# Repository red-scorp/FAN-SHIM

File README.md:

# FAN-SHIM project

FAN-SHIM (mini-HAT), support board for axial fans to cool Raspberry Pi.

Some Pis not require cooling because their CPUs are running in low performance mode.
Some Pis are good with simple passive heat sinks alone.
It's generally recommended to use active coolers, specially if you run Pi's CPU over-clocked.

This boards are designed to be used with standard axial funs with Pi's "Dupont" and standard PC's "Molex" connectors.

## FAN-zero30-SHIM

Raspberry Pi zero 40-pin **FAN-zero30-SHIM** mini-HAT.

Preview:

[Schematics in PDF format](doc/FAN-zero30-SHIM.pdf)

Features:

- locked Pi headers
- 30mm axial fan
- 5V and 3.3V fan power selection
- fan tacho and PWM signal selection
- Pi zero board style
- can be used as SHIM (no headers) or HAT (with headers)

Pins Configuration:

|Fan Pin |Option 1 |Option 2 |
|--------|---------|---------|
|Vfan    |5V\*     |3.3V     |
|tacho   |GPIO16   |GPIO4    |
|PWM     |GPIO12   |GPIO13   |

\*) the pin is connected by default.

CAM files are available.

## FAN-zero25-SHIM

Raspberry Pi zero 40-pin **FAN-zero25-SHIM** mini-HAT.

Preview:

[Schematics in PDF format](doc/FAN-zero25-SHIM.pdf)

Features:

- locked Pi headers
- 25mm axial fan
- 5V and 3.3V fan power selection
- fan tacho and PWM signal selection
- Pi zero board style
- can be used as SHIM (no headers) or HAT (with headers)

Pins Configuration:

|Fan Pin |Option 1 |Option 2 |
|--------|---------|---------|
|Vfan    |5V\*     |3.3V     |
|tacho   |GPIO16   |GPIO4    |
|PWM     |GPIO12   |GPIO13   |

\*) the pin is connected by default.

CAM files are available.

## FAN-zero20-SHIM

Raspberry Pi zero 40-pin **FAN-zero20-SHIM** mini-HAT.

Preview:

[Schematics in PDF format](doc/FAN-zero20-SHIM.pdf)

Features:

- locked Pi headers
- 20mm axial fan
- 5V and 3.3V fan power selection
- fan tacho and PWM signal selection
- Pi zero board style
- can be used as SHIM (no headers) or HAT (with headers)

Pins Configuration:

|Fan Pin |Option 1 |Option 2 |
|--------|---------|---------|
|Vfan    |5V\*     |3.3V     |
|tacho   |GPIO16   |GPIO4    |
|PWM     |GPIO12   |GPIO13   |

\*) the pin is connected by default.

CAM files are available.

## FAN-plus40-SHIM

Raspberry Pi A+/B+ 40-pin **FAN-plus40-SHIM** mini-HAT.

Preview:

[Schematics in PDF format](doc/FAN-plus40-SHIM.pdf)

Features:

- locked Pi headers
- 40mm axial fan
- 5V and 3.3V fan power selection
- fan tacho and PWM signal selection
- Pi A+/B+ board style
- can be used as SHIM (no headers) or HAT (with headers)

Pins Configuration:

|Fan Pin |Option 1 |Option 2 |
|--------|---------|---------|
|Vfan    |5V\*     |3.3V     |
|tacho   |GPIO16   |GPIO4    |
|PWM     |GPIO12   |GPIO13   |

\*) the pin is connected by default.

CAM files are available.

## FAN-plus30-SHIM

Raspberry Pi A+/B+ 40-pin **FAN-plus30-SHIM** mini-HAT.

Preview:

[Schematics in PDF format](doc/FAN-plus30-SHIM.pdf)

Features:

- locked Pi headers
- 30mm axial fan
- 5V and 3.3V fan power selection
- fan tacho and PWM signal selection
- Pi A+/B+ board style
- can be used as SHIM (no headers) or HAT (with headers)

Pins Configuration:

|Fan Pin |Option 1 |Option 2 |
|--------|---------|---------|
|Vfan    |5V\*     |3.3V     |
|tacho   |GPIO16   |GPIO4    |
|PWM     |GPIO12   |GPIO13   |

\*) the pin is connected by default.

CAM files are available.

## Links

- [pinout.xyz](https://pinout.xyz/) - a brilliant resource on topic of Pi's pinout and HATs.
- [raspberrypi/hats](https://github.com/raspberrypi/hats) - Pi's HAT specification.

## How to help

Your contributions as code, resources, or finances are welcome! Please contact me directly via email at andriy.golovnya@gmail.com or through my [GitHub profile](https://github.com/red-scorp).

If you'd like to make a financial contribution, you can donate via [PayPal](http://paypal.me/redscorp) or [Ko-Fi](http://ko-fi.com/redscorp). Your support is greatly appreciated.

Thanks in advance!

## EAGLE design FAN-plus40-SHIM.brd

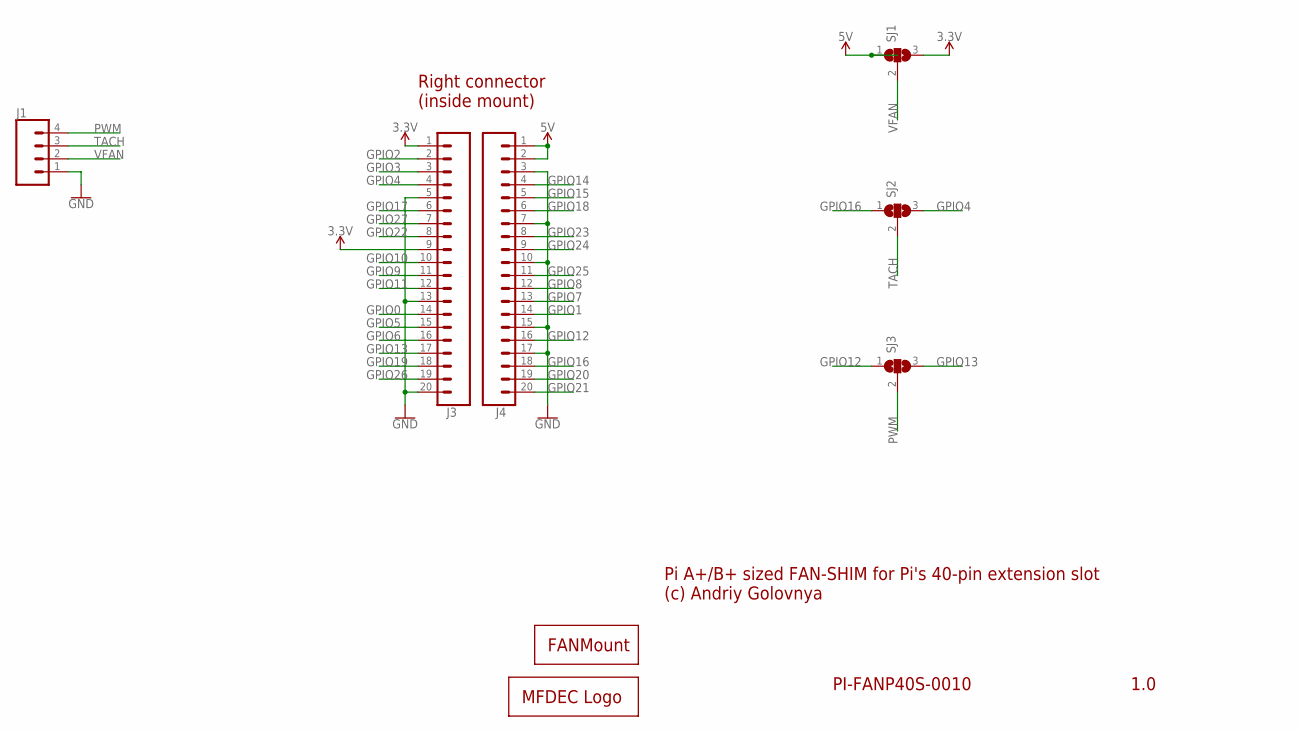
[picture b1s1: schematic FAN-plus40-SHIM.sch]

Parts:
FAN1: FAN40HO
J1: CONN_04; 1X04
J3, J4: CONN_20LOCK; 1X20_LOCK
LOGO1: MFDECLOGO_L_40MM; MFDEC_L_40MM
SJ1, SJ2, SJ3: SJ2; SJ_2

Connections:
3.3V: J3.1, J3.9, SJ1.3
5V: J4.1, J4.2, SJ1.1
GND: J1.1, J3.5, J3.13, J3.20, J4.3, J4.7, J4.10, J4.15, J4.17
GPIO0: J3.14
GPIO1: J4.14
GPIO2: J3.2
GPIO3: J3.3
GPIO4: J3.4, SJ2.3
GPIO5: J3.15
GPIO6: J3.16
GPIO7: J4.13
GPIO8: J4.12
GPIO9: J3.11
GPIO10: J3.10
GPIO11: J3.12
GPIO12: J4.16, SJ3.1
GPIO13: J3.17, SJ3.3
GPIO14: J4.4
GPIO15: J4.5
GPIO16: J4.18, SJ2.1
GPIO17: J3.6
GPIO18: J4.6
GPIO19: J3.18
GPIO20: J4.19
GPIO21: J4.20
GPIO22: J3.8
GPIO23: J4.8
GPIO24: J4.9
GPIO25: J4.11
GPIO26: J3.19
GPIO27: J3.7
PWM: J1.4, SJ3.2
TACH: J1.3, SJ2.2
VFAN: J1.2, SJ1.2

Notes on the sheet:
1.0
PI-FANP40S-0010
Pi A+/B+ sized FAN-SHIM for Pi's 40-pin extension slot (c) Andriy Golovnya
Right connector (inside mount)

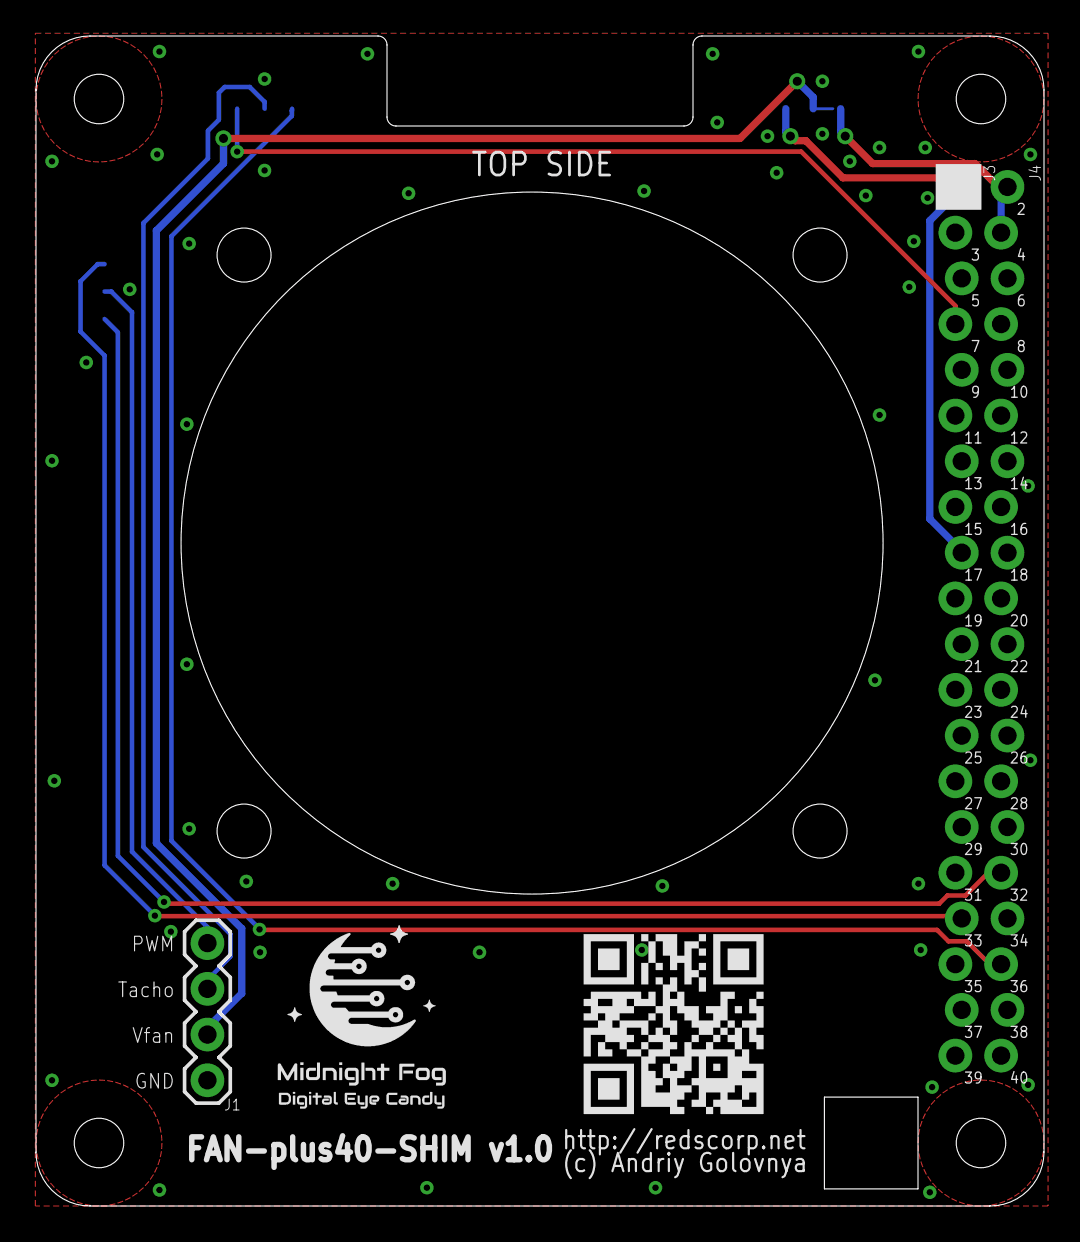
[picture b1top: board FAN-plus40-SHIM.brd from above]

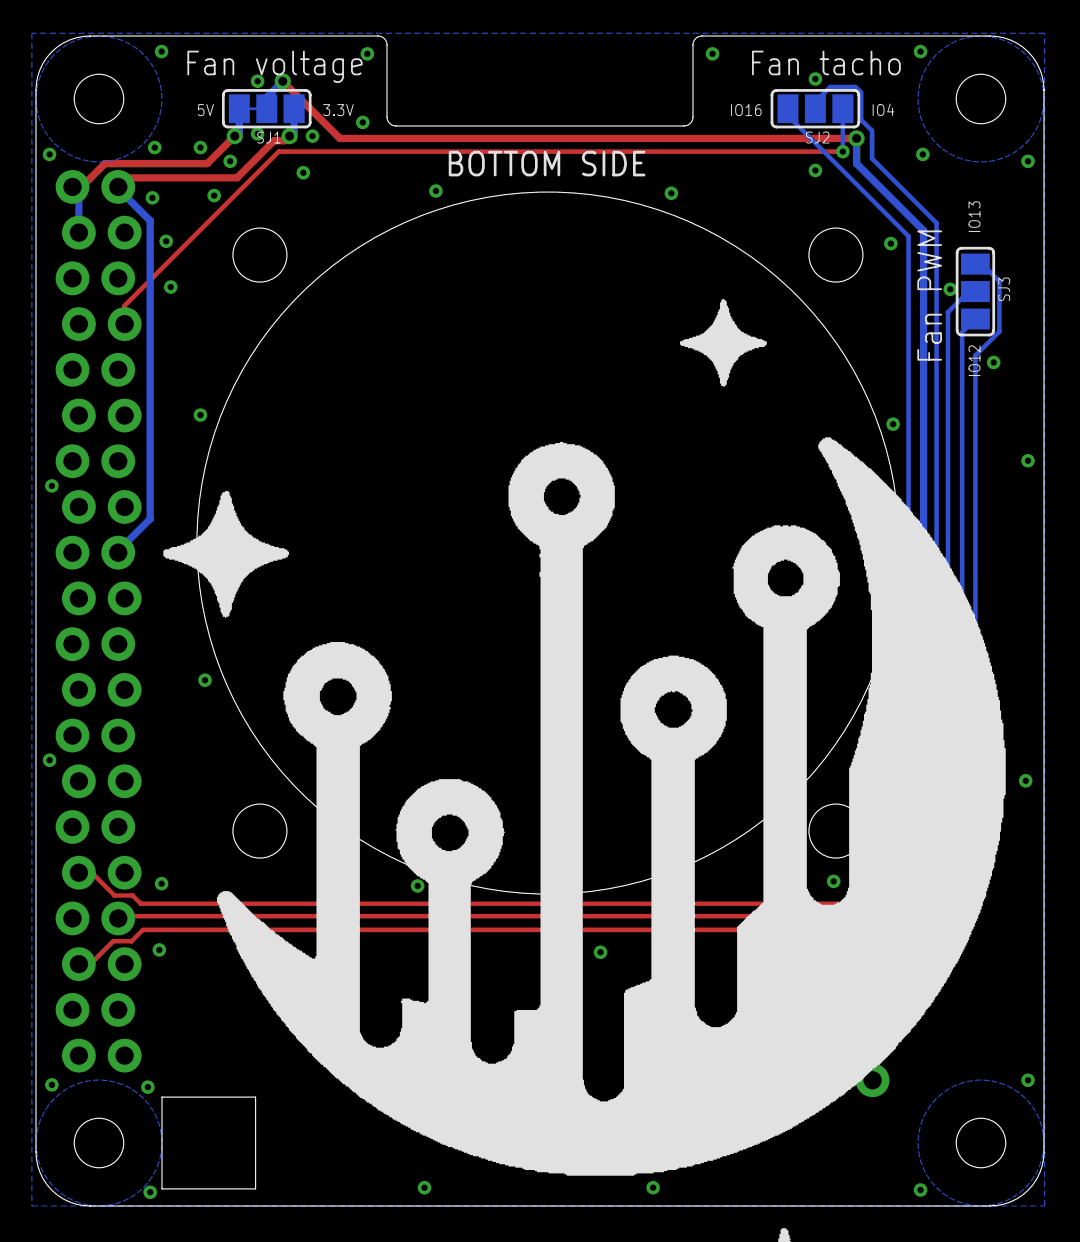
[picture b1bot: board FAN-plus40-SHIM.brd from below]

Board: 2 copper layers, 56.0 x 65.0 mm, 10 parts (4 on the bottom side), 10 nets.

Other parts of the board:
LOGO2: MFDECLOGO_SQ_8MM; MFDEC_SQ_8MM
LOGO3: RSNURL_QR_10MM

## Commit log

2021-01-24 Added basic placement for zero board
2021-01-30 Shaped FAN-zero-SHIM size.
2021-01-30 Renamed boards according to fan sizes.
2021-01-30 Connecting dots.
2021-01-31 Moved some traces around.
2021-01-31 Generated CAM. Generated PDF schematics. Generated PNG preview images.
2021-01-31 Added descriptions.
2021-01-31 Added FUNDING.yml
2021-01-31 Updated descriptions.
2021-02-02 Updated description.
2021-02-19 - Fixed 30mm fan mount hole distance. - Generated new CAM. - Generated new PNG preview image.
2021-02-20 - Fixed VFAN trace on zero30 board. - Generated new CAM. - Generated new PNG preview image.
2021-02-20 - Add 30mm plus version of the board. - Generated CAM. - Generated PNG preview. - Generated PDF schematics. - Updated descriptions.
2021-02-20 - Add 25mm zero version of the board. - Generated CAM. - Generated PNG preview. - Generated PDF schematics. - Updated descriptions.
2021-02-20 - Add 20mm zero version of the board. - Generated CAM. - Generated PNG preview. - Generated PDF schematics. - Updated descriptions.
2021-02-20 - Fixed power trace on zero30 board. - Generated new CAM.
2021-07-29 Make round cutouts in screwing area. Generated CAM files. Generated PNG previews.
2021-12-05 cleanup.
2022-01-24 Added Ko-Fi link
2022-02-06 Updated descriptions
2023-08-28 Updated 'How to help' section.

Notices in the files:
parts and their libraries:
SparkFun-Connectors: Licensing: Creative Commons ShareAlike 4.0 International - https://creativecommons.org/licenses/by-sa/4.0
